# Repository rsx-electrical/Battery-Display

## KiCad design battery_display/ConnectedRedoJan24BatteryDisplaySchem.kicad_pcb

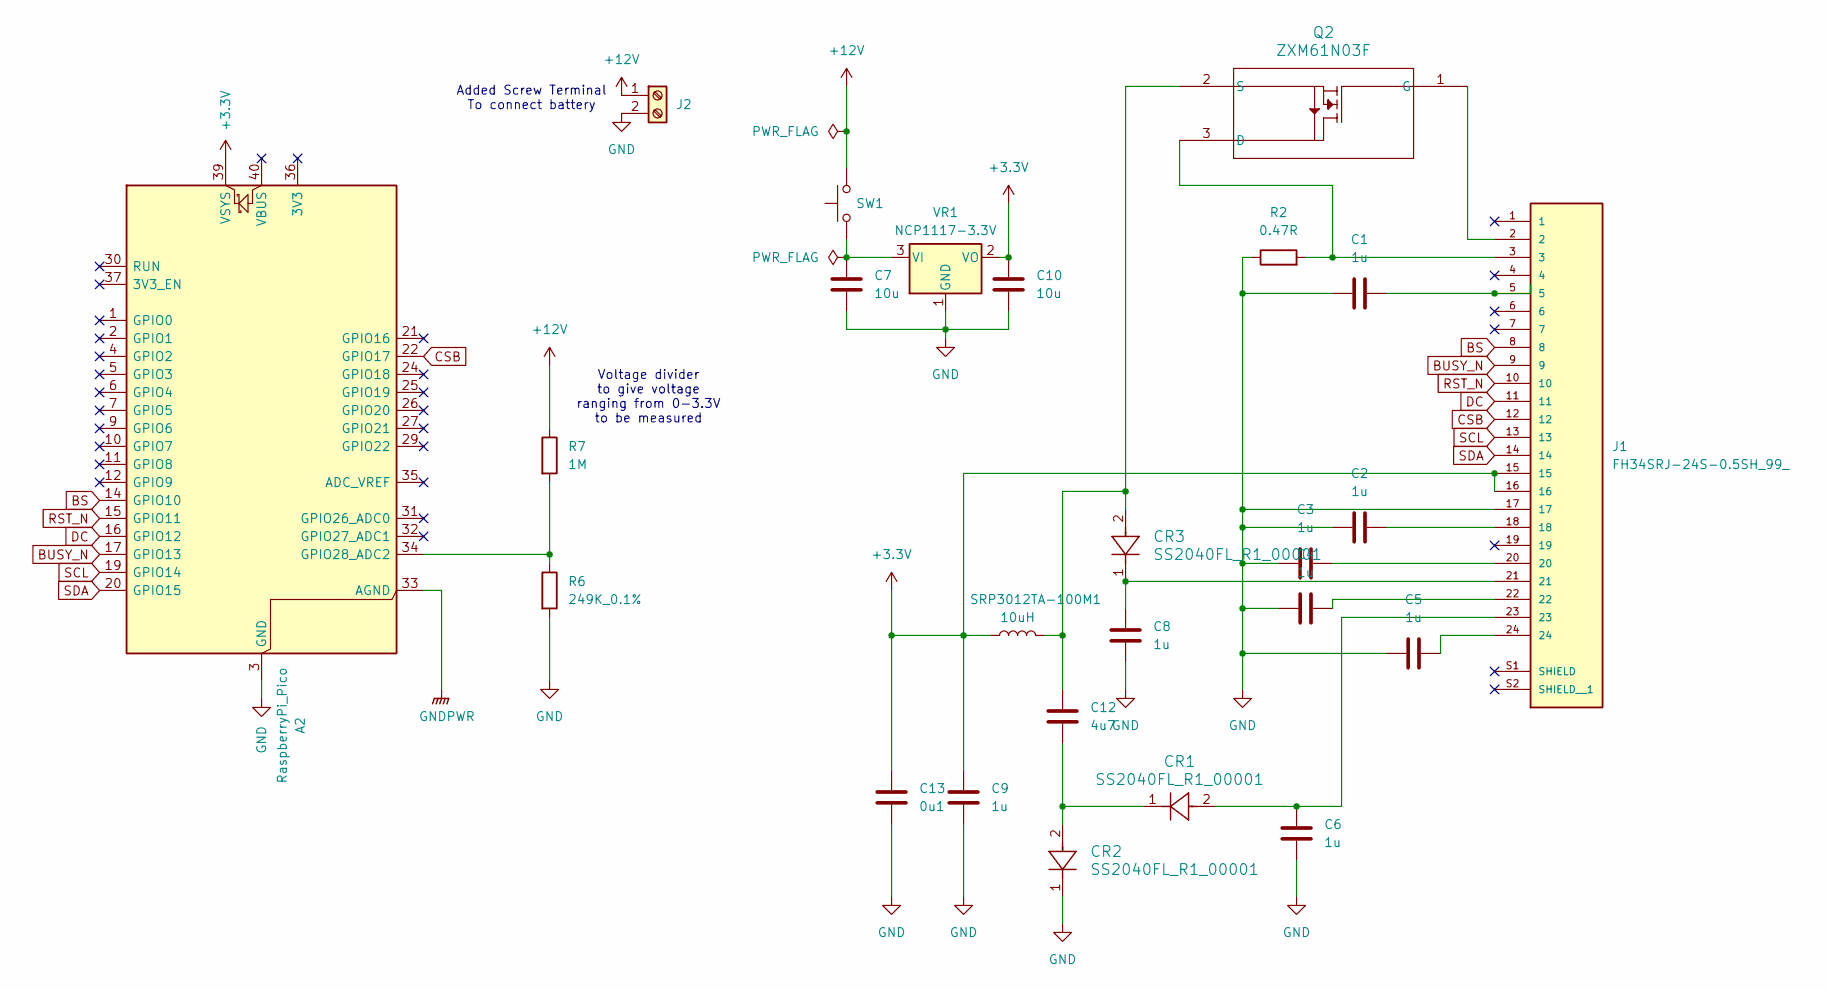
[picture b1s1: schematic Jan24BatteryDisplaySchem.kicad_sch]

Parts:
A2: RaspberryPi_Pico; RaspberryPi_Pico_Common_Unspecified
C1, C2, C3, C4, C5, C6, C8, C9: 1u; C_0805_2012Metric; MPN CL21B105KBFNNNE
C7, C10: 10u; C_0805_2012Metric; MPN GRM21BR61H106KE43L
C12: 4u7; C_0805_2012Metric; MPN CL21A475KAQNNNE
C13: 0u1; C_0603_1608Metric; MPN C1608X7R1H104K080AA
CR1, CR2, CR3: SS2040FL_R1_00001; Nexperia_CFP3_SOD-123W; MPN SS2040FL_R1_00001
J1: FH34SRJ-24S-0.5SH_99_; HRS_FH34SRJ-24S-0.5SH_99_; PARTREV NA
J2: Screw_Terminal_2x2.54; Wurth_691210910002; MPN 691210910002
Q2: ZXM61N03F; SOT-23; MPN ZXM61N03FTA
R2: 0.47R; R_1206_3216Metric; MPN RL1206FR-070R47L
R6: 249K_0.1%; R_0603_1608Metric; MPN RC0603FR-07249KL
R7: 1M; R_0603_1608Metric; MPN ERJ-3EKF1004V
SRP3012TA-100M1: 10uH; IND_SRP3012TA_BRN; MPN SRP3012TA-100M
SW1: Button; FSMSMTR; MPN FSMSMTR
VR1: NCP1117-3.3V; SOT-223-3_TabPin2; MPN NCP1117IST33T3G

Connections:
+3.3V: A2.39 (VSYS), C9.1, C10.1, C13.1, J1.15, J1.16, SRP3012TA-100M1.1, VR1.2 (VO); also elsewhere on the board
+12V: J2.1, R7.1, SW1.2
BS: A2.14 (GPIO10), J1.8
BUSY_N: A2.17 (GPIO13), J1.9
CSB: A2.22 (GPIO17), J1.12
DC: A2.16 (GPIO12), J1.11
GND: A2.3 (GND), A2.8 (GND), A2.13 (GND), A2.18 (GND), A2.23 (GND), A2.28 (GND), A2.38 (GND), C1.1, C2.1, C3.1, C4.1, C5.2, C6.2, C7.2, C8.2, C9.2, C10.2, C13.2, CR2.1, J1.17, J2.2, R2.1, R6.2, VR1.1 (GND)
GNDPWR: A2.33 (AGND)
unnamed: A2.34 (GPIO28_ADC2), R6.1, R7.2
unnamed: C1.2, J1.5
unnamed: C2.2, J1.18
unnamed: C3.2, J1.20
unnamed: C4.2, J1.22
unnamed: C5.1, J1.24
unnamed: C6.1, CR1.2, J1.23
unnamed: C8.1, CR3.1, J1.21
unnamed: C12.2, CR1.1, CR2.2
unnamed: J1.3, Q2.3 (D), R2.2
unnamed: J1.2, Q2.1 (G)
unnamed 19: C12.1, CR3.2, Q2.2 (S), SRP3012TA-100M1.2; also elsewhere on the board
unnamed: C7.1, SW1.1, VR1.3 (VI)
RST_N: A2.15 (GPIO11), J1.10
SCL: A2.19 (GPIO14), J1.13
SDA: A2.20 (GPIO15), J1.14

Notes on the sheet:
Added Screw Terminal To connect battery
Voltage divider to give voltage ranging from 0-3.3V to be measured

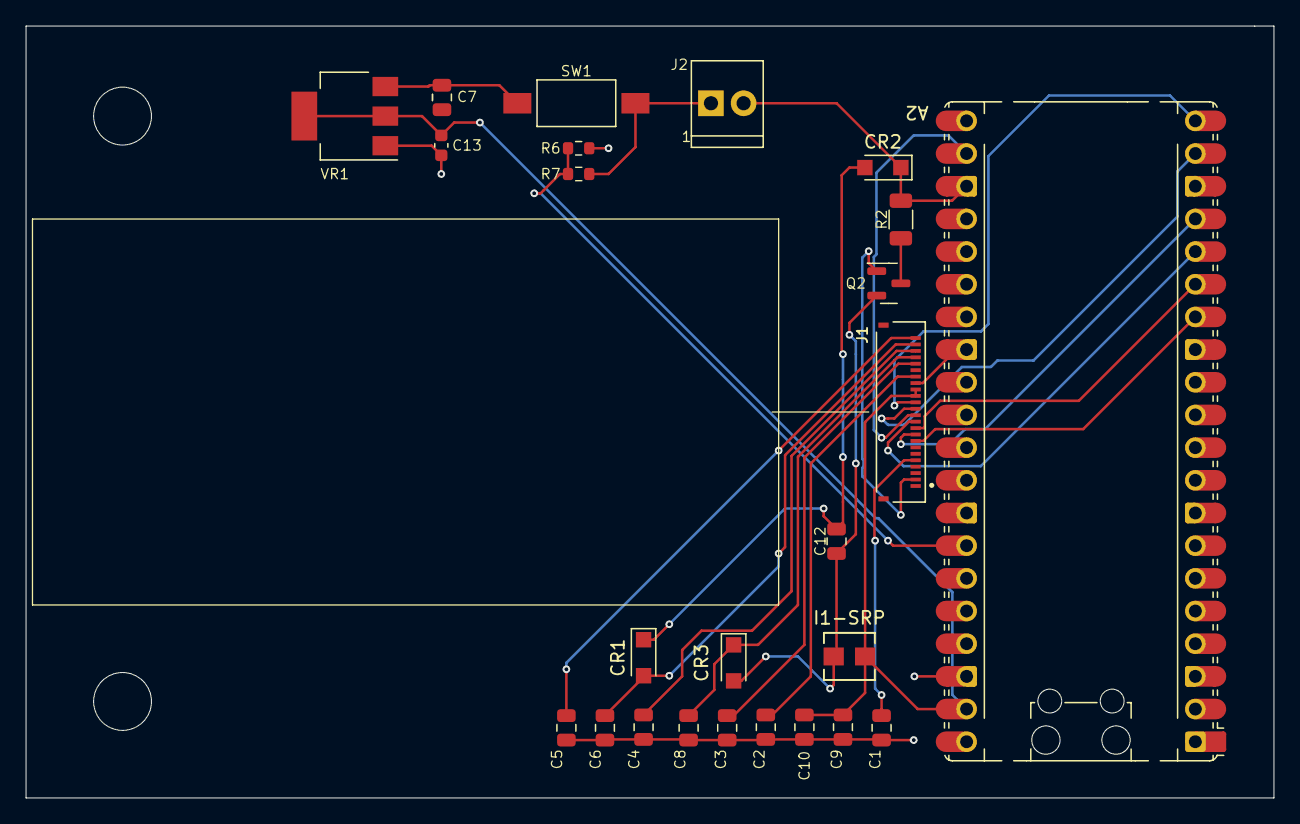
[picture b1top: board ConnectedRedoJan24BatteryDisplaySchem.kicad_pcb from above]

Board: 2 copper layers, 97.0 x 60.0 mm, 27 parts (0 on the bottom side), 23 nets.

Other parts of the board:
H1, H2: M4 PLAIN; MountingHole_4.5mm
I1-SRP: 10uH; IND_SRP3012TA_BRN

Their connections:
+3.3V: I1-SRP.1; also elsewhere on the board
unnamed 19: I1-SRP.2; also elsewhere on the board
